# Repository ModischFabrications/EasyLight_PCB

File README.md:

# EasyLight_PCB

A simple and reusable PCB that can power and control lights both from USB and an internal battery. This will be integrated into multiple other projects of mine. 

The main features are:
1. Uninterrupted power supply for light installations that can hot-swap between USB power and battery backup
2. Integrated charging, protection and load sharing/power path selection of a Li-Ion battery
3. Control of WS2812B, SK6812 and similar digital RGB(W) lights
4. 3 integrated pushbuttons for simple controls
5. Extendable inputs via external buttons
6. Toggle Button to turn off the lamp logic without disconnecting battery charger

Open like regular in KiCad 6. Look into the exports under [Actions/KiCad Exports](https://github.com/ModischFabrications/EasyLight_PCB/actions/workflows/kicad-exports.yml) to see schematics, renderings, exports and more. You will get a few warnings about missing libraries (LCSC and my logos), relink or ignore them. 

This project took around 50 hours of work to finish, from part research to finished PCB(A). Take some time to work through all of it if you want to replicate anything, it's not for the faint-hearted. Do feel invited to donate if you found this useful.

## Fabrication
It's designed to be mostly assembled by JLCPCB's SMT Assembly service, which should make replicating everything pretty easy. The final price should be around 50€ for 10 boards with almost all parts included, you won't get much cheaper if you assemble yourself. 
Check for coupons prior to ordering, there are usually 6..9€ discounts somewhere. I do recommend you invest +1€ for checkups of all files and +1€ for leadfree solder (yes, lead is *that* bad). Do check for correct placement of all parts, JLCPCB has some weird offsets in it's parts. 

Ordering fewer boards is rarely economical: 5 boards cost 42€, because a large part of the cost is "extended part" reel switching for 3$ each and the additional attrition (junked parts). THT parts also incur a flat 3€ "hand soldering" surcharge, you might want to skip them completely.
You might get away ordering fewer if you heavily reuse very few components or limit yourself to basic parts. Paneling could also reduce costs, but you need a large number of small PCBs to make it worthwhile. Panel yourself instead of using their service to save additional 4€.

-> Feel free to deselect parts you don't need from PCBA, connectors or the overpriced ATtiny85 are a good choice. 

## Decisions

### Programming & Debugging
It's not easy to program microcontrollers without a huge markup in size and/or cost. 

The easiest solution is to have a socket on the PCB to program the IC externally and plug it in afterwards. There are no electrical problems with the board itself, it's easy to exchange once killed and you can use basic components. 
There are problems though:
- Stacking PCB - Socket - IC takes at least 10mm in height
- Additional socket to place
- Only THT DIP chips supported

The default option for better boards is to use an "In System Programmer", or ISP in short, that connects directly to the chip. There are some considerations on connected IO, especially on pins usually meant as an input, but it's independent of the actual location and package of the IC. Do note that they can be connected in reverse, which will usually kill everything on your board. 

The traditional AVR-ISP is a 6 pin connector with 2.54mm pitch on the board. This is compatible to generic hookup wires used for every arduino ever made, but needs a bit of space because of the large pitch and THT parts. 

It's possible to use finer connectors with a bit more features, e.g. JST-SH-6, but that will lock you out of the generic programmers and poses additional costs. It will however make programming more reliable and enjoyable.

More elegant solutions depend on "pogo pins" and exposed copper test pads. It's compact and doesn't need any additional parts on the board, but has it's problems with alignment. Hint: Don't try to hold solid pins onto these pads and expect programming to work, you need a bit of spring tension to keep 2x3 pins connected. Pogo pins with large cone heads can actually be used on plated holes meant to solder in AVR-ISPs as well, but are more difficult to find. Another trick is to use vias in the pads itself to align everything, but make sure not to tent/plate them. Make sure to pierce contaminants for boards with cheap plating. 

There is some [great research](http://www.auelectronics.com/forum/index.php?topic=42.0) on these, especially on the [tips used](https://electronics.stackexchange.com/questions/360050/implementing-a-good-connection-for-pogo-pins-in-eagle), [and plating](https://electronics.stackexchange.com/questions/393531/what-pcb-plating-do-i-need-to-use-exposed-copper-pads-with-pogo-pins). Some even [sell premade ones](https://www.tindie.com/products/madworm/tiny-avr-isp-pogo-pin-programming-adapter/), take a look at them for inspiration. 

See [Tag-Connect](https://www.tag-connect.com/) for a commercial solution that's solid and prevents reverse connections. It [seems to have some problems](https://ludzinc.blogspot.com/2013/03/missed-it-by-that-much.html) though and is a very fine 1.27mm pitch. If you buy one, take the solution without mounting holes, the other one is huge.

TLDR: 
- Use the right pogo:
  - cone (1.4mm) for plated holes/vias, can use pads
  - crown for pads with solder
  - round for gold plated pads with repeated contacts
- use pads with 1.27 or 2.54mm pitch
- add via/plated hole to pad to make alignment easier
- use gold plating or apply solder to pads that will be contacted often
- add alignment hole if you feel fancy
-> generic 2.54mm THT pin header holes (ID=1mm, OD=1.7mm) are fine

### Power planning
These boards are planned for two use cases:
1. Docked: Permanent wall power with battery as backup for short durations
2. Mobile: Usually operated by battery, charged whenever needed

The whole system is planned to stay well below 1.5A@5V with either high intensity battery runtimes of <8h or standby battery runtime of 20+ days. 
Battery thresholds are conservative, health is more important than maximized capacities. Buy a bigger battery if you want more runtime. 

Wall Power input is assumed to be larger than power demand by the load + battery, reduce charging current if that is not the case. This usually means >=500mA, depending on use case. 

### Battery Level/Charge Detection
ATtiny85 can read VCC via internal ADC, which makes battery voltage readings easy due to the unregulated output.
There is a slight drop from the power path and other peripherals, but it's probably smaller than the variance of the ADC itself. 

Most chargers also offer a CRG/STAT output, see https://electronics.stackexchange.com/a/624987/217104 on how to read that. 

This can be used to detect 4 states:  
1. Battery empty
2. Battery charging
2. Battery discharging
2. Battery full

### Load sharing/Power Path
The usual solution to charge the battery of a device is to cut off the output, either mechanically with a switch (BAT || SUB) or with a P-FET. This is easy, but is incompatible for UPSs and similar "always-on" use cases.

[Load sharing](https://www.microtype.io/lithium-ion-battery-charger-circuit-load-sharing/) is needed to power the device while charging the battery. Yes, the ubiquitous TP4056 boards [do it wrong](https://www.best-microcontroller-projects.com/tp4056.html). 

Cheap solutions use two diodes, most a P-FET in the battery path, better ones one for each. Add doubled up FETs to prevent body diode conduction and the BOMs balloons up. This application can live with the default solution and just one FET, because input is always higher voltage (/2) and unlimited (/2). Do note the "backwards" P-FET, it's to save the second transistor while blocking reverse current. 

Ideal diodes or PowerMUX would be ideal, but are more expensive. Have a look at [this explanation from TI](https://www.ti.com/lit/an/slvae57b/slvae57b.pdf), especially Figure 8-1/9-3. 

### Button inputs
Using 1 input per Pin is easy to program, but wasteful for MCUs with few IOs. Chaining button to an analog input is much more efficient and can support up to 32 buttons per pin at very detectable 32mV increments. Detecting sequential presses is easy, parallel is more difficult. Smarter chaining could also permit multiple buttons at once with decades (1K, 2K, 4K, ...). See [this explanation](http://www.ignorantofthings.com/2018/07/the-perfect-multi-button-input-resistor.html) or [this one](https://github.com/bxparks/AceButton/blob/develop/docs/resistor_ladder/README.md). 

[This simulation](https://www.falstad.com/circuit/circuitjs.html?ctz=CQAgjCAMB0l3BWcMBMcUHYMGZIA4UA2ATmIxAUgpABZsKBTAWjDACgBnEFFG73-nxR48UcCABmAQwA2HBmwButGqOwIUK0WEJU9tKkn0wEbAE7gMhEOs1gr3EWJ5xz4YTY3vRw0VTDwbjx8toKOfrQYrlz21sGWcU7+krLynN5hYB6+YhDScgoAxjZ4IV7YpdwYmnqw8BAwcA117BYVQgLt4LpiuIEA7iV8OlQ0qt16bADmWp6aY2qEEZBsgwtzQxsrg-GhsVurCRtZal7bGfH78edXAvHXh3hUl9kCNx6hTwdcmJr31eFcikCkEAaFfoD-PAVm00BtsHCcs80NEbIjOoikuJ8mlBgjkUIAQ8dmDynDQud8WEusTNqEqRTDhDwZ0zky7nciW9HlR6ZpGXi-gIvg8uCLhc8sXlUgoLF9PpKIjQoukEdS-lLgWlYfCNREXIddD4BIQEHFuYNTdZQkaDoMrKdNFEyjVDs6wg6wucrRt3QKQO74j7RQHIB0+IHNTjZaGXbHIfxAhYfTazQmAoEuMGTWmkdiZY81aFPYyZngi15y-ylmJzp6RiAqxMoG5PfF6z0oa5iiWvG2AbVoc0mlAWm5bTb8Anla5lE3PmqG-oaIZa6PTFmp0Gt1GCwB7bogQh8UaQUjURrwMhWlBGbiH7BsA-YcjHsQr89GOpwa9m2-iflyEfIA) is also somewhat useful if you want to play around with values. 
Advice: Keep Pullup equal to the smallest resistor and keep their resistances somewhat close together, so that the pressing the largest in parallel to the smallest is still detectable. The internal pullup is fine for one-offs, but varies too much for dependable values, better use an external one. 

Search vor *DAC*, *R-2R* or *resistor ladder* for more references. 

3 Buttons are integrated into the PCB by default, but there are more possibilities by soldering wires into the empty connector next to the buttons to use external ones. 

### Test Points & Extensions
I would like to use this schematic for as much as possible, so there are a few "generics" that might not be always needed. 

### LiPo instead of LiFePo4
LiFePo4 is a great chemistry because it is 3.0V to 3.6V by default, which makes voltage regulators for the ESP32 (also 3.0 to 3.6V) obsolete. 
Sadly, they aren't readily available in small pouches, the smallest ones have AA format, which is too big for our button. 

LiPo has a wide variety of form factors and fits our geometry better, but is 4.2V to 2.7V. 
Discharging to 3V only uses roughly 80% of power. Keeping the minimum voltage high is also healthier for the battery. 
A boost-converter could discharge lower, but it would burn more power when idle. 

This means we need a highly efficient voltage regulator or operate off of a wide range of voltages. 
It needs low I_Q, low V_DO while offering V_OUT of ~3V (to allow for more dropout) at <= 500mA. 
I chose unregulated power because all parts can handle it and it reduces complexity while increasing efficiency. 

Side note: Disposable vapes are a cancer to the environment, but have "free" LiPos in them, which are great to use here. 

### Safety
Short-circuit-resistance of the power leads is archieved using a polyfuse. 
Battery safety is handled by a dedicated chip on the PCB (there is an additional one in most batteries). 

Input ESD & Overvoltage should be handled by the TVS diode. A bidirectional one was chosen to enable the polarity protection later without the TVS interfering. 

Reverse Polarity protection via P-FET according to [this great video](https://www.youtube.com/watch?v=IrB-FPcv1Dc&t=184s).

## Part Selection
Everything is optimized for JLCPCB, because they are great for (cheap) hobby projects. 
[JLCPCB Search](https://jlcpcb.com/parts/) was used for simple part lookup, usually with "basic parts".
[LCSC Search](https://www.lcsc.com/) should show the same parts from the same database, but doesn't add much. 
[JLCParts](https://yaqwsx.github.io/jlcparts/#/) was used to find more complex parts. 
[easyeda2kicad](https://github.com/uPesy/easyeda2kicad.py) to import parts into KiCAD. You should use generic footprints & symbols for simple parts instead. 

Basic parts are given preference, because they are cheaper for assembly service. 

Footprints: 
- THT are dead, SMD is king
- QFN are pain, BGA impossible
- SOT-23-5, SOP-8, SMA and similar are good choices
- 0603 or bigger
-> Soldering by hand should be possible, even if reflow is easier

Generic resistors and capacitors use the [E6 series](https://en.wikipedia.org/wiki/E_series_of_preferred_numbers) for best compatibility.

Some footprints might use minor variations for parts that I already have, sorry for that. 
Others are based on availability and consistency, e.g. 22uF caps are the largest capacity I could get as a cheap basic part in 0603. 

### Microcontroller
Needs: 
- No WiFi
- Small size
- >=3 GPIOs
- Easy integration with PlatformIO
- Works with unregulated 3..5V

Choices:
- Full-size Arduinos are wasted energy, space and cost
- STM32 are industrial use, but not great to integrate into hobbyist projects with arduino libs
- ESP\* are wasteful without WiFi and are 3.3V only
- **ATtiny\*** fit the bill, ATtiny85 to get the most out of the form factor

### Lights
RGBs are easy and cheap to get, but RGBW makes white much easier and cleaner, maybe even more efficient. 
Analog stripes and discrete LEDs were considered, but increase part cost, need more IOs and offer fewer features. 

Use WS2812B for cheap RGB and SK6812 for pretty RGBW. 
APA102/SK9822 are a better version of the WS2812B with 4 instead of 3 wires, which makes great refresh rates and easy timings for complex programs. Imho, they are not necessary for simple lights with few chips. 
I added support for all types in the pinout regardless, leave Pin 3 empty for other chipsets. 

See [FastLED Chipset reference](https://github.com/FastLED/FastLED/wiki/Chipset-reference) for a few more suggestions or [Qwiic LED Stick](https://cdn.sparkfun.com/assets/b/c/9/c/1/Qwiic_LED_Stick_-_Schematic.pdf) for a great hookup reference. 

Signal lines have series resistors (300..500 Ohm) to match impedances and protect the IC from overcurrent, see [this great guide from Adafruit](https://learn.adafruit.com/adafruit-neopixel-uberguide/best-practices) and [this great image](https://forum.arduino.cc/t/arduino-ws2812b-data-pin-resistor/533031/3). They will prevents shorts from overloading the IO while keeping a low profile in relation to the huge impedance of the LEDs. 

Close to the connector are some huge capacitors as well to stabilize LED voltages, but they are smaller than recommended due to the low number of LEDs and my disregard for (aging) electrolyte capacitors. 

### AIO Power Management Chip (disqualified)
IP5306 is a great chip that can do everything at once, including:
1. Protection (with reasonable cutoffs)
2. Charging
3. Powerpath
4. Boost to 5V

But it has a few quirks due to it being designed for powerbanks:
1. Mostly chinese documentation, [small EN translations]()
2. Always boosts to 5V (wasteful, we can handle unfiltered here)
3. **Needs a key press to start and >=50mA to continue operation**
4. Indicators focused on LEDs with multiple variations, making IO readout difficult

A few of these problems can be mitigated by using the I2C variant and [this](https://github.com/bheesma-10/IP5306_I2C) library, but that is still not enough: 

1. Needs 3 additional IOs. 
2. No voltage detection, just basic status
3. More difficult to source from distributors

### TP4056 LiPo Board (disqualified)
Extend with power path, drop in FS312F-G, reduce charging current to <=600mA. Okay, but not great. 

### Charge Controller, Battery Protection, Load Sharing/Power Path
Dedicated parts can be optimised better for these use cases. 
[This video](https://www.youtube.com/watch?v=-SJbdPvgQnE&list=PL68C2022EF3AFB717) is a great summary on what to look for.

#### BMS
BMS ≠ Charger! These components are safety devices and just cut the power. 
They are usually integrated in packs (look for "protected"), but a dedicated one is safer and has healthier thresholds. 
They are usually tiny and behind tape, made with only a DW01-P + 2 MOSFETs. 

- [FS312F-G](https://www.lcsc.com/product-detail/Battery-Management-ICs_Fortune-Semicon-FS312F-G_C82736.html)(0.15€) popular drop-in replacement for DW01-P with better thresholds
  - usually acompanied by [FS8205A](https://www.lcsc.com/product-detail/MOSFETs_FUXINSEMI-FS8205A_C908265.html)(0.06€)
- [**XB8089D0**](https://www.lcsc.com/product-detail/Battery-Management-ICs_XySemi-XB8089D0_C2760005.html)(0.16€) similar, but with **integrated FETs** with compatible performance

#### Charger 
- [TP4056](https://www.lcsc.com/product-detail/Battery-Management-ICs_UMW-Youtai-Semiconductor-Co-Ltd-TP4056_C725790.html)(0.08€!) always available and default for chinese PCBs, but little [(EN)](https://dlnmh9ip6v2uc.cloudfront.net/datasheets/Prototyping/TP4056.pdf) documentation and bigger package (SOP-8). 1A, 1.5%
- [MCP73831-2\*](https://www.lcsc.com/product-detail/Battery-Management-ICs_Microchip-Tech-MCP73831T-2ACI-OT_C424093.html)(0.76€) widely available and often used in open projects. Great documentation and package (SOT-23-5). 0.5A, 0.75%
- [**BQ21040**](https://www.lcsc.com/product-detail/Battery-Management-ICs_Texas-Instruments-BQ21040DBVR_C202311.html)(0.68€) often recommended, with great documentation. 0.8A, 1%, Timer, NTC support. 
  - Other BQ24\* have difficult packages and are more expensive
- LTC\* are nice in theory, but surprisingly expensive from China (>1.50€)
- MCP73871 is an awesome solution with integrated power path, switching and more, but only come in QFN-20
- ...

#### Power Path 
Power Path Controllers: 
- BQ2403x : AIO, but QFN only
- ...
-> Not feasible for cheap hobby projects; would use MCP73871 if going QFN

Ideal Diodes/Load Switch/PowerMux:  
More complex ICs with internal transistors, but great performance. Usually more expensive, build for bigger loads.
- [LTC4412](https://www.lcsc.com/product-detail/Gate-Drive-ICs_Analog-Devices-LTC4412ES6-PBF_C107968.html)(2,73€!!): good docs, but controller only and stupid expensive
- [LM66100](https://www.lcsc.com/product-detail/Power-Distribution-Switches_Texas-Instruments-LM66100DCKR_C2869734.html)(0.54€): well known and great performance, okay price for ID (0.5uA, 0.01V, 1.5A)
- [MT9700](https://www.lcsc.com/product-detail/Power-Distribution-Switches_XI-AN-Aerosemi-Tech-MT9700_C89855.html)(0.05!) : Common part, crazy cheap, okay performance. Not sure if proper diode? (1A)
- [MAX40203](https://www.lcsc.com/product-detail/Power-Distribution-Switches_Maxim-Integrated-MAX40203AUK-T_C2653639.html)(0.65€) : great fit (1A)
- [LTC4415](https://www.lcsc.com/products/Power-Distribution-Switches_969.html?keyword=LTC4415)(6.44€) Dual package, exact match, nice! Huge package, 16 leads, expensive :/ (4A)
- [LM66200](https://www.lcsc.com/product-detail/Power-Distribution-Switches_Texas-Instruments-LM66200DRLR_C3235556.html)(0.43€) Dual package, cheap, perfect use-case. Tiny package (SOT-583) :/
-> Use two of these if you need high power, high efficiency. Not worth it for small runs, use default solution of P-FET + D

P-FET:  
I > 1.5A, R_DSon < 60mR and V_GS < 0.5 .. 1.5V. 
R is important to loose as little battery energy as possible. Extremely low V_GS could switch too soon due to diode, too high would increase R_DSon.
- [DMP1045U](https://www.lcsc.com/product-detail/MOSFETs_Diodes-Incorporated-DMP1045U-7_C177033.html)(0.37€) popular, great stats and package (4A 31mΩ@4.5V)
- [DMP2035U](https://www.lcsc.com/product-detail/MOSFETs_Diodes-Incorporated-Diodes-Incorporated-DMP2035U-7_C110499.html)(0.12€) good values, fair price, good documentation (3.6A 35mΩ@4.5V)
- [WST2339](https://www.lcsc.com/product-detail/MOSFETs_Winsok-Semicon-Winsok-Semicon-WST2339_C148354.html)(0.12€) great (7.1A 19mΩ@4.5V)
- [AP2335](https://www.lcsc.com/product-detail/MOSFETs_ALLPOWERShenZhen-Quan-Li-Semiconductor-ALLPOWERShenZhen-Quan-Li-Semiconductor-AP2335_C2828582.html)(0.08€) great (7A 19mΩ@4.5V)
- [SI2301S](https://www.lcsc.com/product-detail/MOSFETs_MDD-Microdiode-Electronics-SI2301S_C427389.html)(0.01€!!) with good stats for great price (2.3A 70mΩ@4.5V)
- [**AO3415**](https://www.lcsc.com/product-detail/MOSFETs_Guangdong-Hottech-Guangdong-Hottech-AO3415_C181094.html)(0.04€) good values and very available, somewhat known (4A 41mΩ@4.5V)
- ...
Most should be pin compatible, feel free to exchange however wanted. 

Diode:  
I > 1.5A, I_r < 50uA and V_f < 0.4V.
Problem: I_r and V_f usually counter each other. Former is important [to keep the FET closed](https://electronics.stackexchange.com/questions/293353/load-sharing-charging-circuit-for-lithium-polymer), latter for efficient wall power because of the waste heat. 
- MBR120 : well known, but max 1A, high leakage (>=1mA)
- [SS14](https://www.lcsc.com/product-detail/Schottky-Barrier-Diodes-SBD_MDD-Microdiode-Electronics-SS14_C2480.html)(0.01€): Well known, basic part, bad values (550mV@1A, 0.5..10mA)
- [**SS34**](https://www.lcsc.com/product-detail/Schottky-Barrier-Diodes-SBD_MDD-Microdiode-Electronics-SS34_C8678.html)(0.03€) : Default, basic part, okay values (500mV@3A, 0.2..6mA)
- [SS54](https://www.lcsc.com/product-detail/Schottky-Barrier-Diodes-SBD_Slkor-SLKORMICRO-Elec-SS54_C513478.html) ? (550mV@5A, 0.5..20mA)
- SB220 : known, but THT
- 1N5817 : somewhat known, but THT. also with 8/9 postfix
- [MBR0520LT1G](https://www.lcsc.com/product-detail/Schottky-Barrier-Diodes-SBD_onsemi-MBR0520LT1G_C23848.html)(0.10€) : (385mV@500mA, 0.075..5mA)
- [MBRS320](https://www.lcsc.com/product-detail/Schottky-Barrier-Diodes-SBD_onsemi-MBRS3201T3G_C236150.html)(0.37€) : expensive, but good values for a regular diode
- [SL22-E3/52T](https://www.lcsc.com/product-detail/Schottky-Barrier-Diodes-SBD_Vishay-Intertech-SL22-E3-52T_C142616.html)(0.37€) expensive for it's value (440mV@2A, 0.4..10mA)
- SD103AWS : great at blocking, not great voltage drop (600mV@200mA, <0.05uA)
- [RSX201VAM30](https://www.lcsc.com/product-detail/Schottky-Barrier-Diodes-SBD_ROHM-Semicon-RSX201VAM30TR_C308755.html)(0.08€) seems like a good pick? (460mV@1.5A, 0.007 .. 0.03mA)
- [PMEG3010ER](https://www.lcsc.com/product-detail/Schottky-Barrier-Diodes-SBD_Nexperia-PMEG3010ER-115_C456106.html)(0.11€) (360mV@1A, 0.6 .. 1.5mA)
- ...

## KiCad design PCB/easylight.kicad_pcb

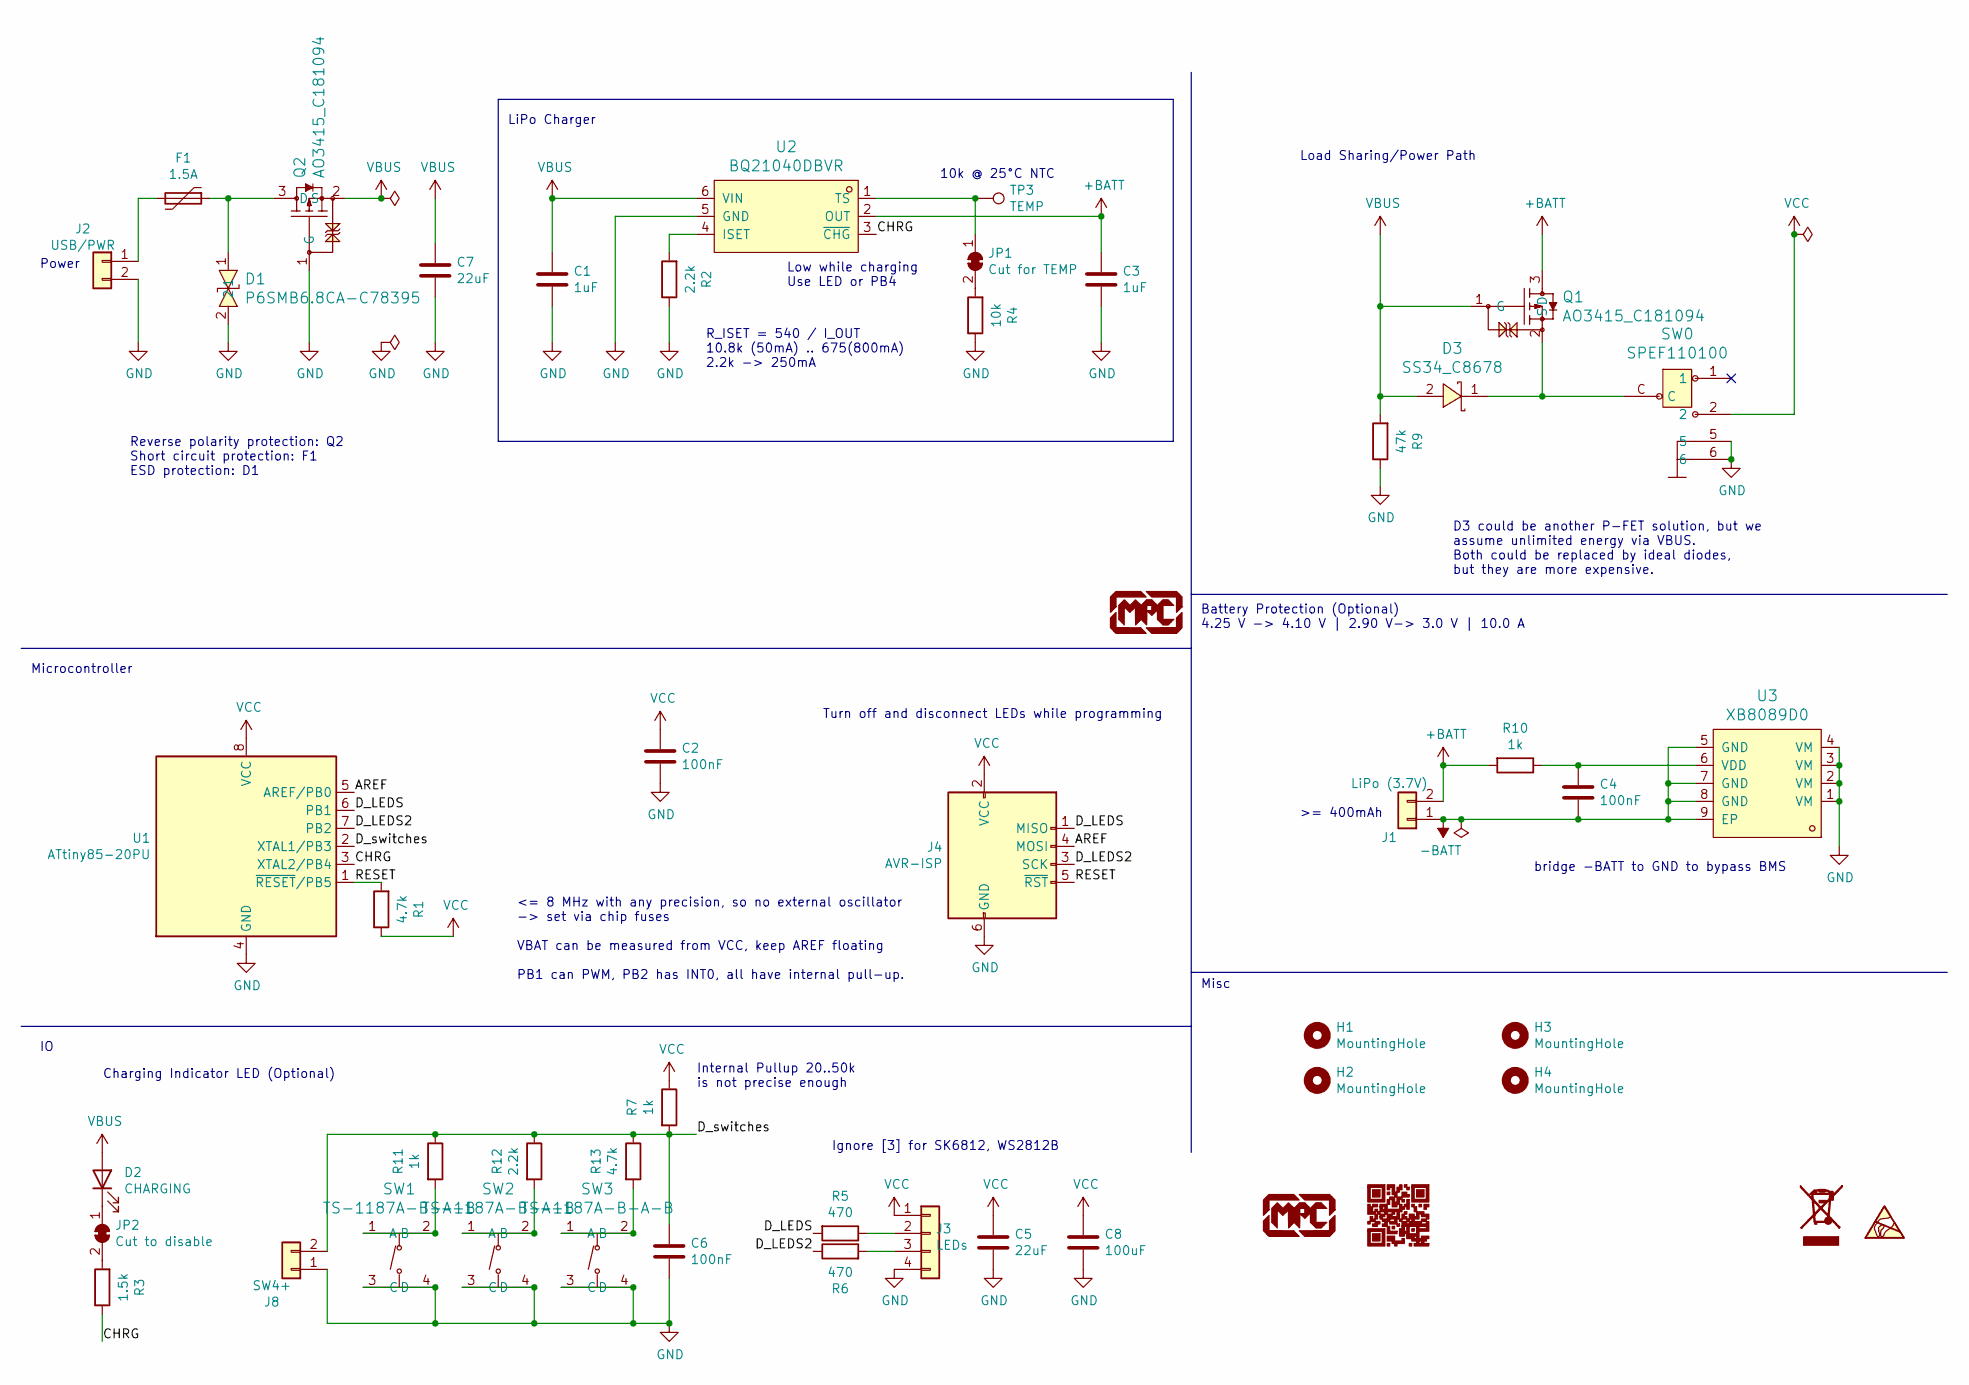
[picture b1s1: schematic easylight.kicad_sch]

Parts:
C1, C3: 1uF; C_0603_1608Metric; LCSC Part C15849
C2, C4, C6: 100nF; C_0603_1608Metric; LCSC Part C14663
C5, C7: 22uF; C_0603_1608Metric; LCSC Part C59461
C8: 100uF; C_1206_3216Metric_Pad1.33x1.80mm_HandSolder; LCSC Part C15008
D1: P6SMB6.8CA-C78395; SMB_L4.6-W3.6-LS5.3-BI; LCSC Part C78395
D2: CHARGING; LED_0603_1608Metric_Pad1.05x0.95mm_HandSolder; JLC Part Basic Part
D3: SS34_C8678; SMA_L4.3-W2.6-LS5.2-RD; LCSC Part C8678
F1: 1.5A; Fuse_1206_3216Metric_Pad1.42x1.75mm_HandSolder; LCSC Part C883133
G1: LOGO; WEEE-Logo_4.2x6mm_SilkScreen
G2: LOGO; MF_QR_7mm
H1, H2, H3, H4: MountingHole; MountingHole_3.2mm_M3_Pad_Via_NC
J1: LiPo (3.7V); JST_XH_B2B-XH-A_1x02_P2.50mm_Vertical; LCSC Part C158012
J2: USB/PWR; JST_XH_B2B-XH-A_1x02_P2.50mm_Vertical; LCSC Part C158012
J3: LEDs; JST_XH_B4B-XH-A_1x04_P2.50mm_Vertical; LCSC Part C144395
J4: AVR-ISP; 3x2 CopperPad 2.54mm
J8: SW4+; PinHeader_1x02_P2.54mm_Vertical
JP1: Cut for TEMP; SolderJumper-2_P1.3mm_Bridged_RoundedPad1.0x1.5mm
JP2: Cut to disable; SolderJumper-2_P1.3mm_Bridged_RoundedPad1.0x1.5mm
L1: LOGO; mpc_logo_5mm
L2: LOGO; mpc_logo_10mm
Q1, Q2: AO3415_C181094; SOT-23-3; LCSC Part C181094
R1, R13: 4.7k; R_0603_1608Metric_Pad0.98x0.95mm_HandSolder; LCSC Part C23162
R2, R12: 2.2k; R_0603_1608Metric_Pad0.98x0.95mm_HandSolder; LCSC Part C4190
R3: 1.5k; R_0603_1608Metric_Pad0.98x0.95mm_HandSolder; LCSC Part C22843
R4: 10k; R_0603_1608Metric_Pad0.98x0.95mm_HandSolder; LCSC Part C25804
R5, R6: 470; R_0603_1608Metric_Pad0.98x0.95mm_HandSolder; LCSC Part C23179
R7, R10, R11: 1k; R_0603_1608Metric_Pad0.98x0.95mm_HandSolder; LCSC Part C21190
R9: 47k; R_0603_1608Metric_Pad0.98x0.95mm_HandSolder; LCSC Part C25819
SW0: SPEF110100; SW-TH_SPEF110100_fixed; LCSC Part C115366
SW1, SW2, SW3: TS-1187A-B-A-B; SW-SMD_4P-L5.1-W5.1-P3.70-LS6.5-TL-2; LCSC Part C318884
SYM1: SYM_ESD_Small; ESD-Logo_6.6x6mm_SilkScreen
TP3: TEMP; TestPoint_THTPad_D2.0mm_Drill1.0mm
U1: ATtiny85-20PU; DIP-8_W7.62mm; LCSC Part C965497
U2: BQ21040DBVR; SOT-23-6_L2.9-W1.6-P0.95-LS2.8-BR; LCSC Part C202311
U3: XB8089D0; SOIC-8-1EP_3.9x4.9mm_P1.27mm_EP2.514x3.2mm; LCSC Part C2760005

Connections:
+BATT: C3.1, J1.2, Q1.3 (D), R10.2, U2.2 (OUT)
-BATT: C4.2, J1.1, U3.5 (GND), U3.7 (GND), U3.8 (GND), U3.9 (EP)
/AREF: J4.4 (MOSI), U1.5 (AREF/PB0)
/CHRG: R3.1, U1.3 (XTAL2/PB4), U2.3 (~CHG)
/D_LEDS: J4.1 (MISO), R5.2, U1.6 (PB1)
/D_LEDS2: J4.3 (SCK), R6.1, U1.7 (PB2)
/D_switches: C6.1, J8.2, R7.2, R11.1, R12.1, R13.1, U1.2 (XTAL1/PB3)
/RESET: J4.5 (~RST), R1.2, U1.1 (~RESET/PB5)
GND: C1.2, C2.2, C3.2, C5.2, C6.2, C7.2, C8.2, D1.2, J2.2, J3.4, J4.6 (GND), J8.1, Q2.1 (G), R2.1, R4.1, R9.1, SW0.5, SW0.6, SW1.3 (C), SW1.4 (D), SW2.3 (C), SW2.4 (D), SW3.3 (C), SW3.4 (D), U1.4 (GND), U2.5 (GND), U3.1 (VM), U3.2 (VM), U3.3 (VM), U3.4 (VM)
unnamed: C4.1, R10.1, U3.6 (VDD)
unnamed: D1.1, F1.1, Q2.3 (D)
unnamed: D2.1 (K), JP2.1 (A)
unnamed: D3.1, Q1.2 (S), SW0.C
unnamed: F1.2, J2.1
unnamed: J3.2, R5.1
unnamed: J3.3, R6.2
unnamed: JP1.1 (A), TP3.1, U2.1 (TS)
unnamed: JP1.2 (B), R4.2
unnamed: JP2.2 (B), R3.2
unnamed: R2.2, U2.4 (ISET)
unnamed: R11.2, SW1.1 (A), SW1.2 (B)
unnamed: R12.2, SW2.1 (A), SW2.2 (B)
unnamed: R13.2, SW3.1 (A), SW3.2 (B)
VBUS: C1.1, C7.1, D2.2 (A), D3.2, Q1.1 (G), Q2.2 (S), R9.2, U2.6 (VIN)
VCC: C2.1, C5.1, C8.1, J3.1, J4.2 (VCC), R1.1, R7.1, SW0.2, U1.8 (VCC)

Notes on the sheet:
Microcontroller
Reverse polarity protection: Q2 Short circuit protection: F1 ESD protection: D1
Turn off and disconnect LEDs while programming
LiPo Charger
Power
<= 8 MHz with any precision, so no external oscillator -> set via chip fuses VBAT can be measured from VCC, keep AREF floating PB1 can PWM, PB2 has INT0, all have internal pull-up.
D3 could be another P-FET solution, but we assume unlimited energy via VBUS. Both could be replaced by ideal diodes, but they are more expensive.
bridge -BATT to GND to bypass BMS
Internal Pullup 20..50k is not precise enough
Low while charging Use LED or PB4
>= 400mAh
Battery Protection (Optional) 4.25 V -> 4.10 V | 2.90 V-> 3.0 V | 10.0 A
10k @ 25°C NTC
Load Sharing/Power Path
Ignore [3] for SK6812, WS2812B
Charging Indicator LED (Optional)
R_ISET = 540 / I_OUT 10.8k (50mA) .. 675(800mA) 2.2k -> 250mA
Misc

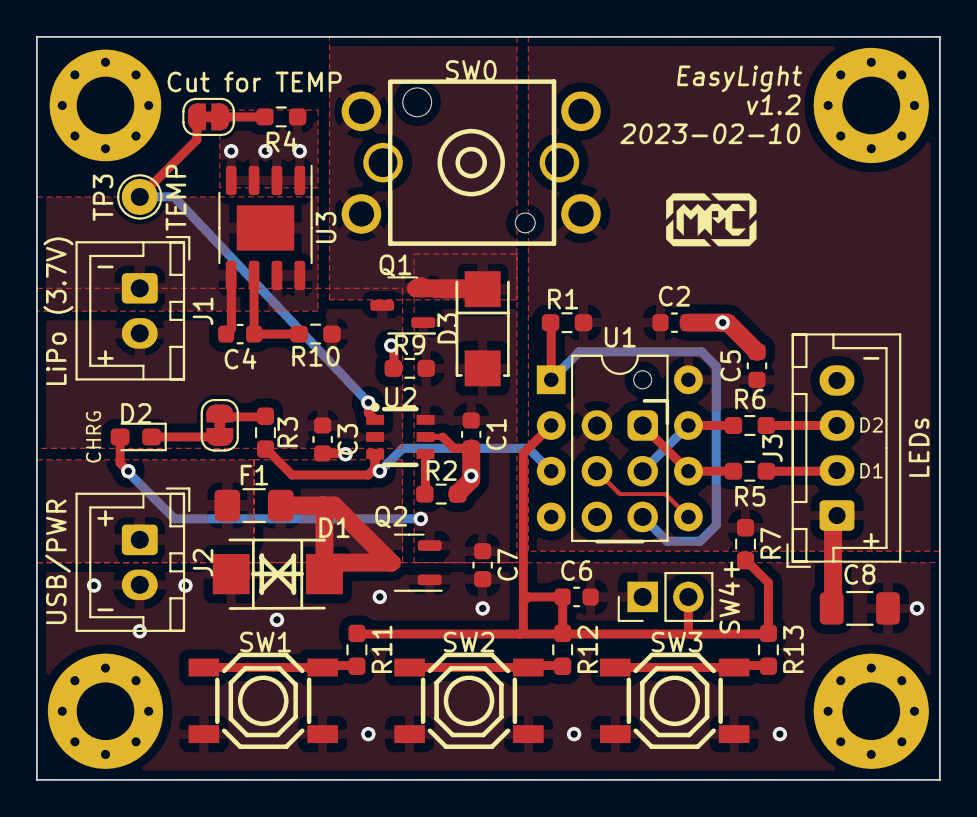
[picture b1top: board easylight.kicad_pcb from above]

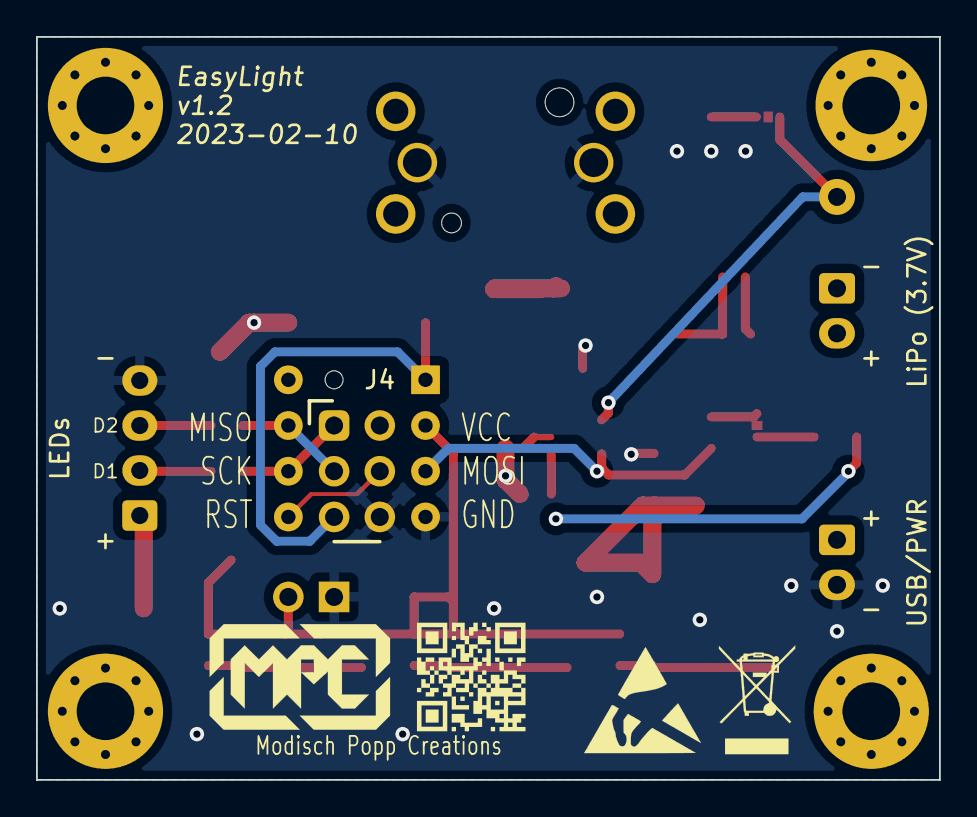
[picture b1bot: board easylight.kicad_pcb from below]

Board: 2 copper layers, 50.2 x 41.3 mm, 50 parts (5 on the bottom side), 25 nets.

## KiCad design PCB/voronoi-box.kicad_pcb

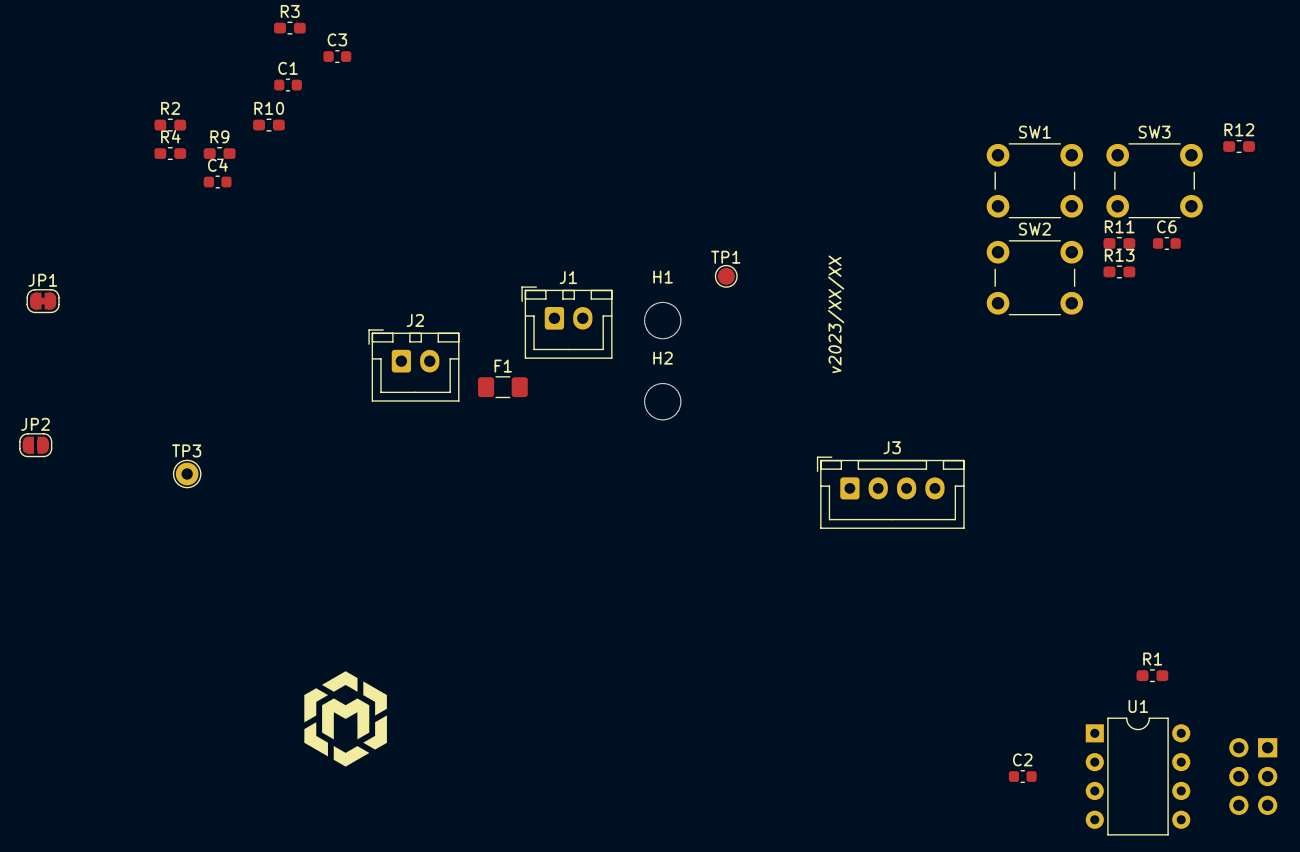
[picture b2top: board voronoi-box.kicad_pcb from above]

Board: 2 copper layers, 30 parts (1 on the bottom side), 17 nets, no tracks yet.

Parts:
C1, C3: 1uF; C_0603_1608Metric
C2, C4, C6: 100nF; C_0603_1608Metric
F1: 1A; Fuse_1206_3216Metric_Pad1.42x1.75mm_HandSolder
H1, H2: MountingHole; MountingHole_3.2mm_M3_DIN965
J1: LiPo (1S/3.7V); JST_XH_B2B-XH-A_1x02_P2.50mm_Vertical
J2: USB/PWR; JST_XH_B2B-XH-A_1x02_P2.50mm_Vertical
J3: LEDs; JST_XH_B4B-XH-A_1x04_P2.50mm_Vertical
J4: AVR-ISP-6; PinHeader_2x03_P2.54mm_Vertical
JP1: Cut for NTC; SolderJumper-2_P1.3mm_Bridged_RoundedPad1.0x1.5mm
JP2: Join without BMS; SolderJumper-2_P1.3mm_Open_RoundedPad1.0x1.5mm
L1: MF_Logo; mf_logo_10mm
R1, R13: 4.7k; R_0603_1608Metric_Pad1.05x0.95mm_HandSolder
R2: 2k; R_0603_1608Metric_Pad1.05x0.95mm_HandSolder
R3: 1.5k; R_0603_1608Metric_Pad1.05x0.95mm_HandSolder
R4: 10k; R_0603_1608Metric_Pad1.05x0.95mm_HandSolder
R9: 47k; R_0603_1608Metric_Pad1.05x0.95mm_HandSolder
R10, R11: 1k; R_0603_1608Metric_Pad1.05x0.95mm_HandSolder
R12: 2.2k; R_0603_1608Metric_Pad1.05x0.95mm_HandSolder
SW1: SW_1; SW_PUSH_6mm_H4.3mm
SW2: SW_2; SW_PUSH_6mm_H4.3mm
SW3: SW_3; SW_PUSH_6mm_H4.3mm
TP1: AREF; TestPoint_Pad_D1.5mm
TP3: TEMP; TestPoint_THTPad_D2.0mm_Drill1.0mm
U1: ATtiny85-20PU; DIP-8_W7.62mm

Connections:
+BATT: C3.1, J1.1, R10.2
-BATT: C4.2, J1.2, JP2.1
/AREF: J4.4, TP1.1, U1.5
/D_LEDS: J3.2, J4.1, U1.6
/D_LEDS2: J3.3, J4.3, U1.7
/D_switches: C6.1, R11.1, R12.1, R13.1, U1.2
/RESET: J4.5, R1.2, U1.1
GND: C1.2, C2.2, C3.2, C6.2, J2.2, J3.4, J4.6, JP2.2, R2.1, R4.1, R9.1, SW1.1, SW2.1, SW3.1, U1.4
unnamed: C4.1, R10.1
unnamed: F1.2, J2.1
unnamed: JP1.1, TP3.1
unnamed: JP1.2, R4.2
unnamed: R11.2, SW1.2
unnamed: R12.2, SW2.2
unnamed: R13.2, SW3.2
VBUS: C1.1, F1.1, R9.2
VCC: C2.1, J3.1, J4.2, R1.1, R3.2, U1.8

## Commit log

2023-01-10 create repo based on CallbackButton
2023-01-10 update readme for EasyLight
2023-01-10 fix workflow trigger
2023-01-10 remove old stuff from schematic, add battery protection, add a lot of components to Readme
2023-01-13 extend Readme with a huge knowledge drop, create new power path with dedicated parts, add ISP, use analog mux for buttons, try to fix CI
2023-01-13 add more readme comments and links, add capacitors and more part numbers, fix lib ref
2023-01-14 rename to easylight, add comments and TODOs
2023-01-14 remove broken refs in CI
2023-01-14 add (THT) part for attiny85, rename
2023-01-14 add TVS for ESD protection, another P-FET for reverse polarity protection
2023-01-15 layout PCB, add series resistors for LEDs, remove unused components and add some cosmetics; ratsnest WIP
2023-01-15 use fixed path for CI
2023-01-15 simplify CI to always run, it's fast enough
2023-01-15 minor cleanup
2023-01-16 add dedicated pullup for resistor ladder, add docs, finish routing of PCB
2023-01-16 Create LICENSE
2023-01-16 label rev1, add date, try to fix kibot build
2023-01-24 add additional capacitor, make data resistors 470R, add template texts in preparation for KiCAD 6, extend readme
2023-01-24 migrate to kicad 6, fix some DRM (clearance still broken), point CI to new files
2023-01-24 relink schematics and footprints, move C, update everything
2023-01-25 update readme, cleanup libs
2023-01-27 migrate kibot to v6, refine exports
2023-01-27 hide orphaned filter tag, fix ci output
2023-01-27 fix output naming, readd brd file
2023-01-27 fix LCSC part column, fix artefact name
2023-01-27 try fetching the date from another source
2023-01-28 fix ci naming again again
2023-01-29 fix ci, i can't even
2023-01-29 fix ci, i can't even 2
2023-01-29 fix ci, i can't even 3
2023-01-29 fix ci with double quotes
2023-01-29 extend CI with a few tests and cleanup existing exports
2023-01-29 retry, skip test for now
2023-01-29 CI: make board blue for visibility, try printing schematic png
2023-01-29 print schematic as pdf for now
2023-01-29 fix names, include tests, include run id in export name
2023-01-29 introduce tests into new files, test selective diffs
2023-01-29 introduce tests into new files, test selective diffs (2)
2023-01-29 try tests, fix some typos, try to introduce enclosing directory
2023-01-29 fix kicost
2023-01-29 fix populate, disable kicost
2023-01-29 disable populate
2023-01-29 remove colliding connector, add button extension connector, declare v1.0
2023-01-29 add permission for releases
2023-02-03 use specific isp connector that has polarity marker, update revision to v1.1, set board colors
2023-02-03 fix new footprint
2023-02-03 cleanup action, release with proper zip
2023-02-03 move kibot configs
2023-02-03 fix ci release
2023-02-09 add more labels, replace broken SOT23 with generic part, update version, cleanup part descriptions
2023-02-09 fix kibot config
2023-02-09 fix kibot config again
2023-02-09 use generic part for SOIC-8, ignore another lib warning
2023-02-10 extend readme
2023-02-10 improve fills, add qr code, improve silkscreen labels

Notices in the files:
PCB/voronoi-box.kicad_pcb:
© Modisch Popp Creations
